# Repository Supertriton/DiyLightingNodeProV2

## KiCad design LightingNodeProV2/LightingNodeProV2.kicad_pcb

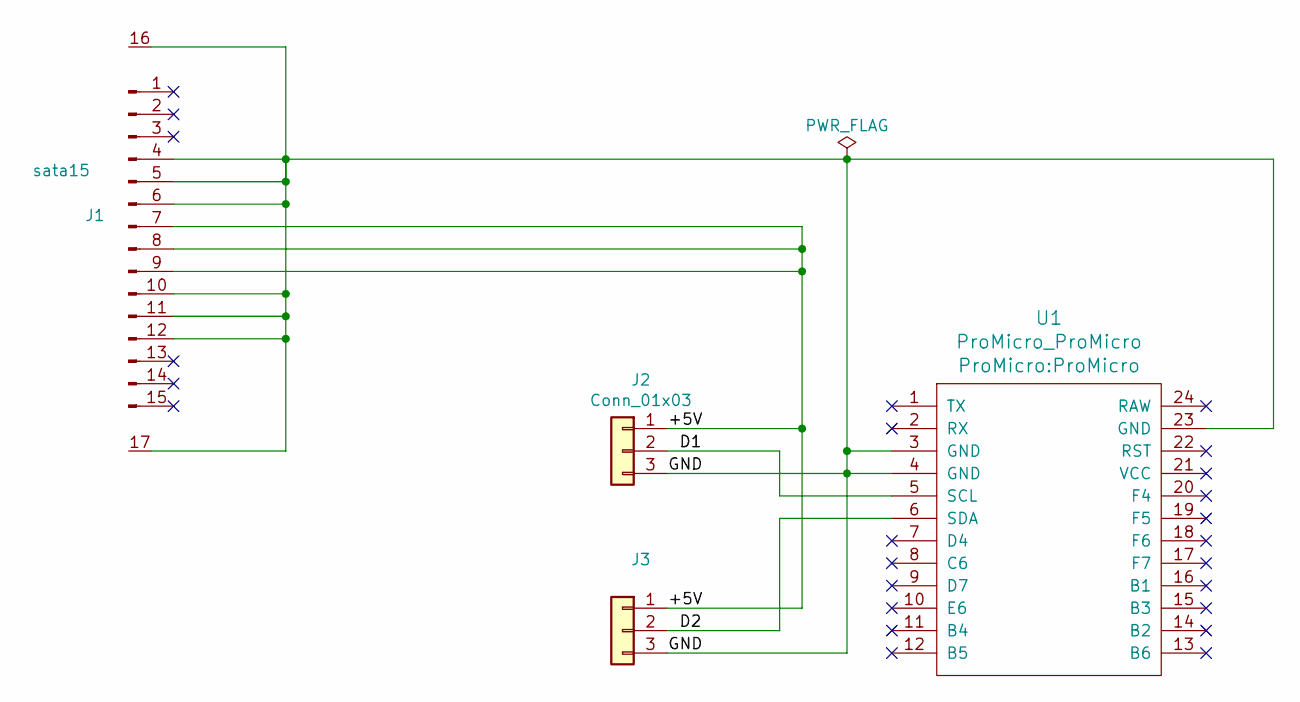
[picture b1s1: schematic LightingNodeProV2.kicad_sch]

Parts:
J1: sata15; satapwrtest
J2, J3: Conn_01x03; 705530002
U1: ProMicro_ProMicro; ProMicro

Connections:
/+5V: J1.7, J1.8, J1.9, J2.1, J3.1
/D1: J2.2, U1.5 (SCL)
/D2: J3.2, U1.6 (SDA)
/GND: J1.4, J1.5, J1.6, J1.10, J1.11, J1.12, J1.16 (GND), J1.17 (GND), J2.3, J3.3, U1.3 (GND), U1.4 (GND), U1.23 (GND)

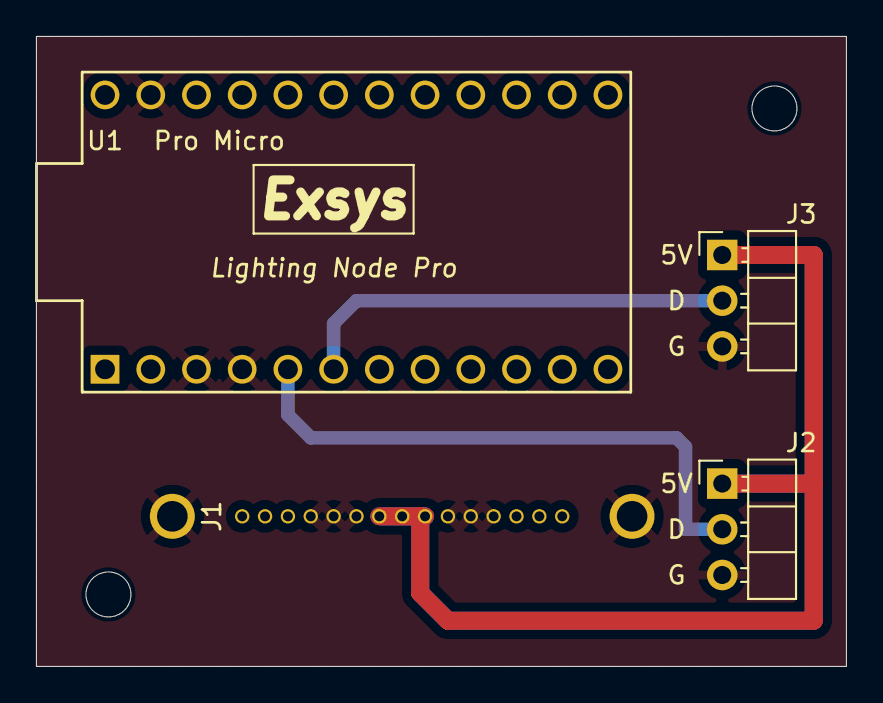
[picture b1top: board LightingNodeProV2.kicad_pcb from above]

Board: 2 copper layers, 45.0 x 35.0 mm, 4 parts (0 on the bottom side), 4 nets.

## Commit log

2023-04-10 Start
    New start
2023-04-10 edit
